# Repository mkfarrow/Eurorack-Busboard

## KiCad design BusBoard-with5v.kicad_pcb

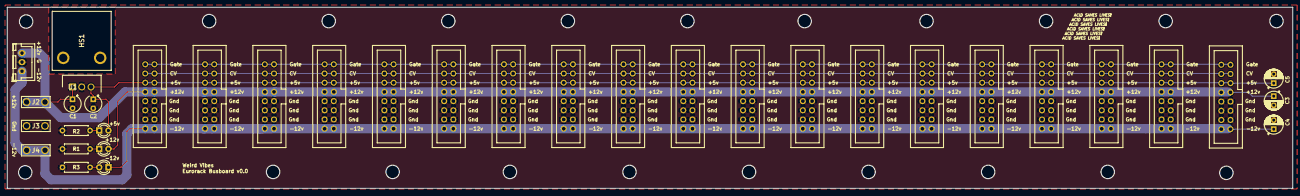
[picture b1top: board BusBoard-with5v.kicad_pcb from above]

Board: 2 copper layers, 355.0 x 50.0 mm, 36 parts (0 on the bottom side), 9 nets.

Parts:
C1: 0.33 uF; CP_Radial_Tantal_D4.5mm_P2.50mm
C2: 0.1 uF; CP_Radial_Tantal_D4.5mm_P2.50mm
C3, C4, C5: CP1; CP_Radial_D5.0mm_P2.50mm
D1, D2, D3: LED; LED_D3.0mm
HS1: Heatsink; E2AT22025E
J1: JST-XH connector; JST_XH_B3B-XH-A_1x03_P2.50mm_Vertical
J2, J3, J4: Q.C.; 638491
J5, J6, J7, J8, J9, J10, J11, J12, J13, J14, J15, J16, J17, J18, J19, J20, J21, J22, J23: Conn_02x08_Odd_Even; IDC-Header_2x08_P2.54mm_Vertical
R1, R2, R3: 1k2; R_Axial_DIN0207_L6.3mm_D2.5mm_P7.62mm_Horizontal
U1: uA7805; TO254P465X1016X1883-3P

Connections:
+5V: C2.1, C5.1, D2.2, J5.11, J5.12, J6.11, J6.12, J7.11, J7.12, J8.11, J8.12, J9.11, J9.12, J10.11, J10.12, J11.11, J11.12, J12.11, J12.12, J13.11, J13.12, J14.11, J14.12, J15.11, J15.12, J16.11, J16.12, J17.11, J17.12, J18.11, J18.12, J19.11, J19.12, J20.11, J20.12, J21.11, J21.12, J22.11, J22.12, J23.11, J23.12, U1.3
+12V: C1.1, C3.1, D1.2, J1.3, J2.1, J2.2, J5.9, J5.10, J6.9, J6.10, J7.9, J7.10, J8.9, J8.10, J9.9, J9.10, J10.9, J10.10, J11.9, J11.10, J12.9, J12.10, J13.9, J13.10, J14.9, J14.10, J15.9, J15.10, J16.9, J16.10, J17.9, J17.10, J18.9, J18.10, J19.9, J19.10, J20.9, J20.10, J21.9, J21.10, J22.9, J22.10, J23.9, J23.10, U1.1
-12V: C4.1, D3.1, J1.1, J4.1, J4.2, J5.1, J5.2, J6.1, J6.2, J7.1, J7.2, J8.1, J8.2, J9.1, J9.2, J10.1, J10.2, J11.1, J11.2, J12.1, J12.2, J13.1, J13.2, J14.1, J14.2, J15.1, J15.2, J16.1, J16.2, J17.1, J17.2, J18.1, J18.2, J19.1, J19.2, J20.1, J20.2, J21.1, J21.2, J22.1, J22.2, J23.1, J23.2
/CV: J5.13, J5.14, J6.13, J6.14, J7.13, J7.14, J8.13, J8.14, J9.13, J9.14, J10.13, J10.14, J11.13, J11.14, J12.13, J12.14, J13.13, J13.14, J14.13, J14.14, J15.13, J15.14, J16.13, J16.14, J17.13, J17.14, J18.13, J18.14, J19.13, J19.14, J20.13, J20.14, J21.13, J21.14, J22.13, J22.14, J23.13, J23.14
/Gate: J5.15, J5.16, J6.15, J6.16, J7.15, J7.16, J8.15, J8.16, J9.15, J9.16, J10.15, J10.16, J11.15, J11.16, J12.15, J12.16, J13.15, J13.16, J14.15, J14.16, J15.15, J15.16, J16.15, J16.16, J17.15, J17.16, J18.15, J18.16, J19.15, J19.16, J20.15, J20.16, J21.15, J21.16, J22.15, J22.16, J23.15, J23.16
GND: C1.2, C2.2, C3.2, C4.2, C5.2, J1.2, J3.1, J3.2, J5.3, J5.4, J5.5, J5.6, J5.7, J5.8, J6.3, J6.4, J6.5, J6.6, J6.7, J6.8, J7.3, J7.4, J7.5, J7.6, J7.7, J7.8, J8.3, J8.4, J8.5, J8.6, J8.7, J8.8, J9.3, J9.4, J9.5, J9.6, J9.7, J9.8, J10.3, J10.4, J10.5, J10.6, J10.7, J10.8, J11.3, J11.4, J11.5, J11.6, J11.7, J11.8, J12.3, J12.4, J12.5, J12.6, J12.7, J12.8, J13.3, J13.4, J13.5, J13.6, J13.7, J13.8, J14.3, J14.4, J14.5, J14.6, J14.7, J14.8, J15.3, J15.4, J15.5, J15.6, J15.7, J15.8, J16.3, J16.4, J16.5, J16.6, J16.7, J16.8, J17.3, J17.4, J17.5, J17.6, J17.7, J17.8, J18.3, J18.4, J18.5, J18.6, J18.7, J18.8, J19.3, J19.4, J19.5, J19.6, J19.7, J19.8, J20.3, J20.4, J20.5, J20.6, J20.7, J20.8, J21.3, J21.4, J21.5, J21.6, J21.7, J21.8, J22.3, J22.4, J22.5, J22.6, J22.7, J22.8, J23.3, J23.4, J23.5, J23.6, J23.7, J23.8, R1.2, R2.2, R3.1, U1.2
unnamed: D1.1, R1.1
unnamed: D2.1, R2.1
unnamed: D3.2, R3.2
